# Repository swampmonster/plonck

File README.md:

# plonck

An attempt at making a planck-compatible pcb with bluetooth  

## Current status:
### Rev A0 (NOT RECOMMENDED FOR PRODUCTION, READ STATUS)
I've received and built this version and it works fine but i made the mistake of wiring up the GND and VBUS pins on the ESD chip incorrectly.  
Thankfully those are the middle pins and simply desoldering and turning the chip around solves the problem.  
Update: Finally had time to test the load sharing circuitry and i had the pinout of the mosfet setup incorrectly which requires bodge wires to fix.  
If you are looking to get boards made from this revision you need to be aware of this but my recommendation would be to wait for the next one.

## Rev B0
This should address all the issues in A0 while also adding some features that were not previously present such as:  
- Leds for charge and bootloader status.
- Voltage divider for charge monitoring.
- SMD USB port so it can be mounted by JLC.

Boards have been ordered but not yet received so production is still not recommended.

## License
The project is licensed under [CERN-OHL-S](LICENSE) (see [LICENSE](LICENSE) file) with the exceptions of:
- The [MX_Alps_Hybrid](MX_Alps_Hybrid) directory which is licensed under the [MIT License](https://opensource.org/licenses/MIT) and is made by [ai03](https://github.com/ai03-2725/MX_Alps_Hybrid).
- The [USB4085-GF-A_REVA](USB4085-GF-A_REVA) directory which is licensed under the [Creative Commons Attribution-ShareAlike 4.0 International License](https://creativecommons.org/licenses/by-sa/4.0/) and comes from [SnapEDA](https://www.snapeda.com/parts/USB4085-GF-A/Global%20Connector%20Technology/view-part/?ref=global%20connector%20technology_in&t=usb4085).
- The [PTS525SM15SMTR2LFS](PTS525SM15SMTR2LFS) directory which is licensed under the [Creative Commons Attribution-ShareAlike 4.0 International License](https://creativecommons.org/licenses/by-sa/4.0/) and comes from [SnapEDA](https://www.snapeda.com/parts/PTS525SM15SMTR2%20LFS/C&K/view-part/?ref=search&t=PTS525).
- The [SM02B-SRSS-TB_LF__SN_](SM02B-SRSS-TB_LF__SN_) directory which is licensed under the [Creative Commons Attribution-ShareAlike 4.0 International License](https://creativecommons.org/licenses/by-sa/4.0/) and comes from [SnapEDA](https://www.snapeda.com/parts/SM02B-SRSS-TB%28LF%29%28SN%29/JST%20Sales/view-part/447499).
- The [ul_SI2301CDST1GE3](ul_SI2301CDST1GE3) directory which is licensed under the terms provided in the Terms and Conditions on [Ultra Librarian](https://www.ultralibrarian.com/)

## Thanks
Huge shoutout to [4pplet](https://github.com/4pplet) for tons of advice and help.

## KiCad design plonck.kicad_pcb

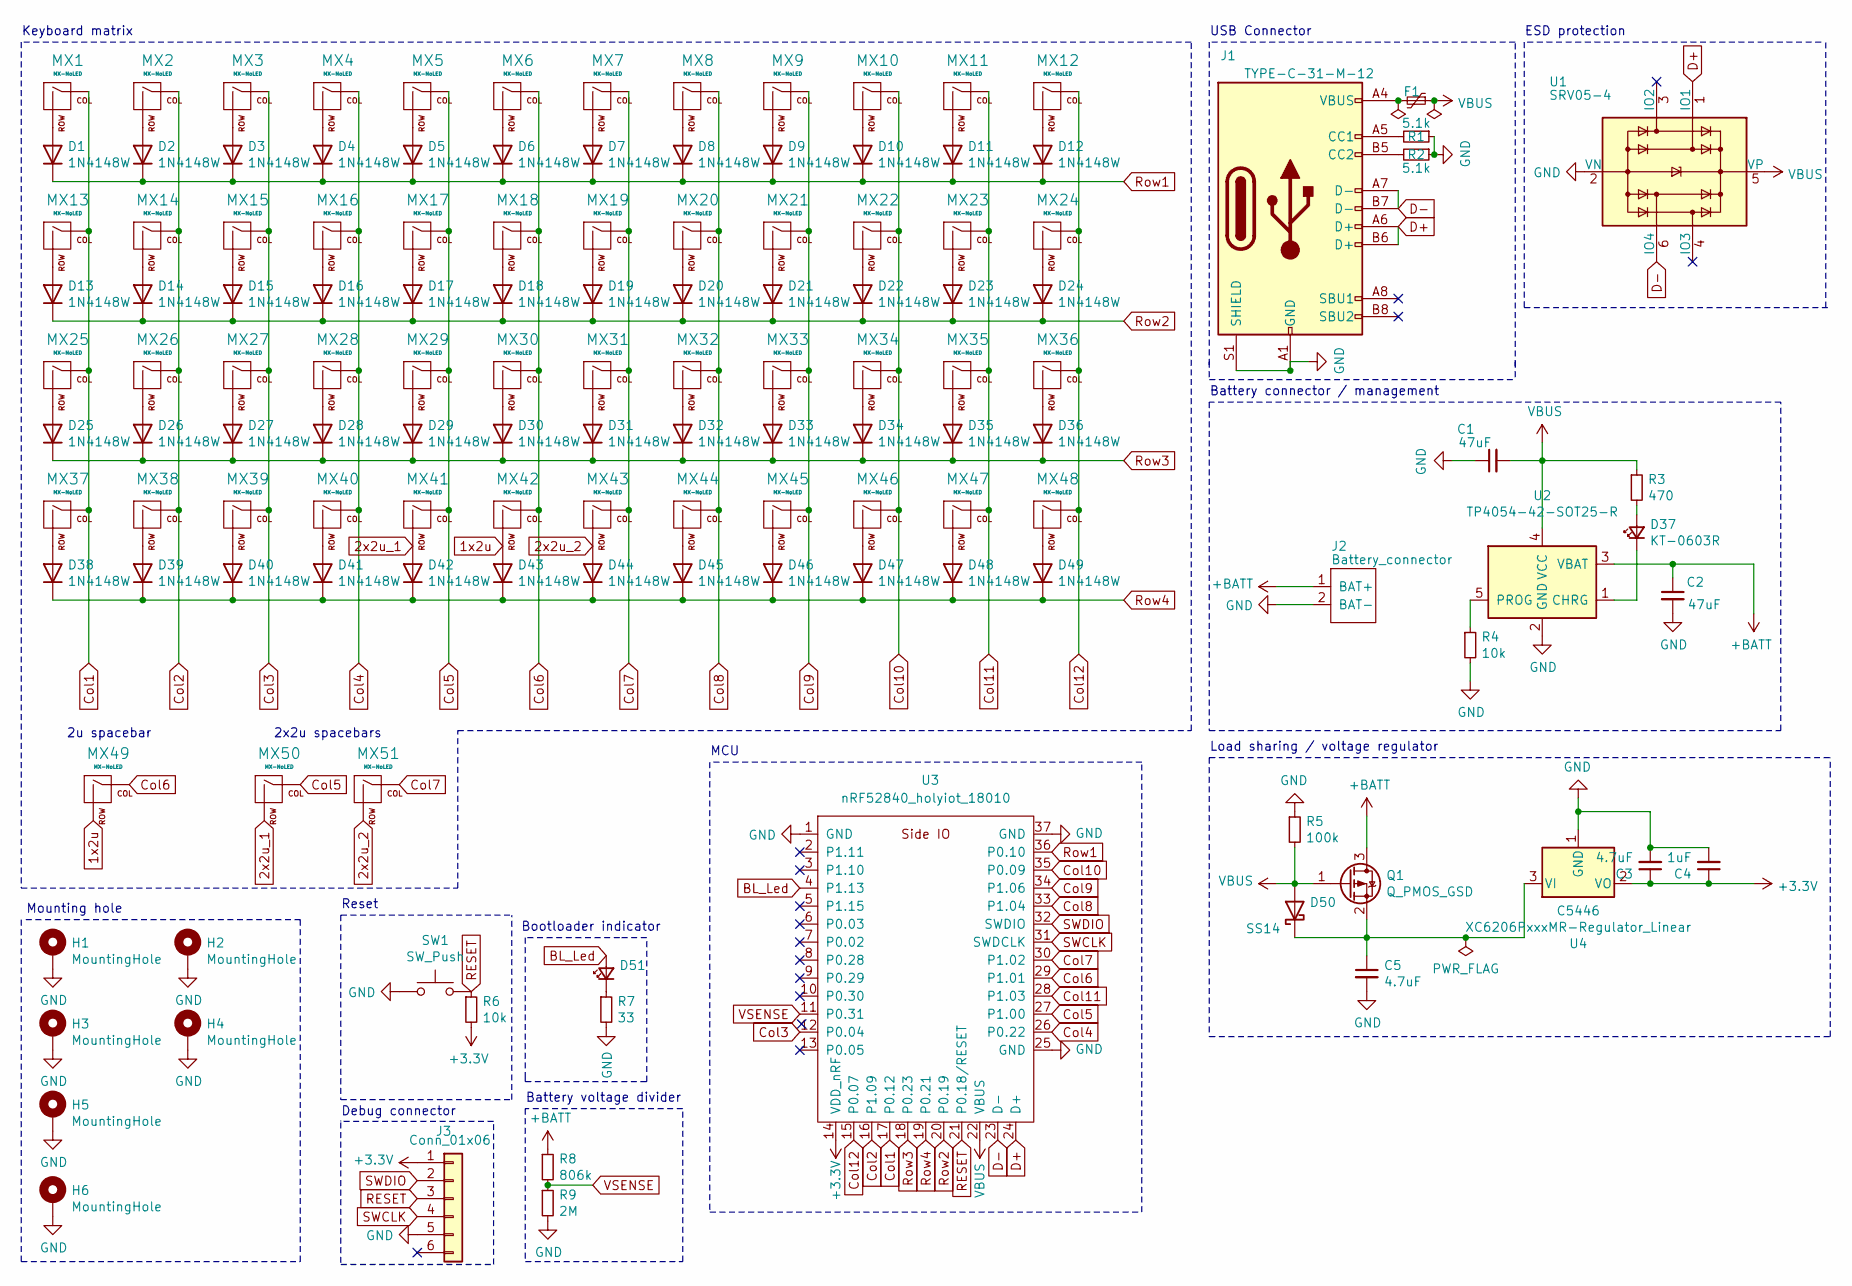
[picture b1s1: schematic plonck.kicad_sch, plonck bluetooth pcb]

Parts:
C1, C2: 47uF; C_1206_3216Metric; LCSC C96123
C3, C5: 4.7uF; C_0603_1608Metric; LCSC C19666
C4: 1uF; C_0603_1608Metric; LCSC C15849
D1, D2, D3, D4, D5, D6, D7, D8, D9, D10, D11, D12, D13, D14, D15, D16, D17, D18, D19, D20, D21, D22, D23, D24, D25, D26, D27, D28, D29, D30, D31, D32, D33, D34, D35, D36, D38, D39, D40, D41, D42, D43, D44, D45, D46, D47, D48, D49: 1N4148W; D_SOD-123; LCSC C402213
D37: KT-0603R; LED_0603_1608Metric; LCSC C2286
D50: SS14; D_SMA; LCSC C2480
D51: 19-217/BHC-ZL1M2RY/3T; LED_0603_1608Metric; LCSC C72041
F1: SMD Fuse Fast Blow 500mA; Fuse_1206_3216Metric; LCSC C182974
H1, H2, H3, H4, H5, H6: MountingHole; MountingHole_2.7mm_M2.5_Pad_TopBottom
J1: TYPE-C-31-M-12; USB_C_Receptacle_HRO_TYPE-C-31-M-12; LCSC C165948
J2: Battery_connector; SM02B-SRSS-TB(LF)(SN)
J3: Conn_01x06; Tag-Connect_TC2030-IDC-NL_2x03_P1.27mm_Vertical
MX1, MX2, MX3, MX4, MX5, MX6, MX7, MX8, MX9, MX10, MX11, MX12, MX13, MX14, MX15, MX16, MX17, MX18, MX19, MX20, MX21, MX22, MX23, MX24, MX25, MX26, MX27, MX28, MX29, MX30, MX31, MX32, MX33, MX34, MX35, MX36, MX37, MX38, MX39, MX40, MX41, MX42, MX43, MX44, MX45, MX46, MX47, MX48: MX-NoLED; MX-1U-NoLED
MX49, MX50, MX51: MX-NoLED; MX-2U-ReversedStabilizers-NoLED
Q1: Q_PMOS_GSD; SI2301CDS-T1-GE3; LCSC C10487
R1, R2: 5.1k; R_0603_1608Metric; Digikey RMCF0603JT5K10TR-ND
R3: 470; R_0603_1608Metric; Digikey RMCF0603JT470RTR-ND
R4, R6: 10k; R_0603_1608Metric; LCSC C25804
R5: 100k; R_0603_1608Metric; Digikey RMCF0603JG100KTR-ND
R7: 33; R_0603_1608Metric; LCSC C23140
R8: 806k; R_0603_1608Metric; LCSC C23250
R9: 2M; R_0603_1608Metric; LCSC C22976
SW1: SW_Push; SW_Push_SPST_NO_Alps_SKRK; LCSC C115357
U1: SRV05-4; SOT-23-6; LCSC C782797
U2: TP4054-42-SOT25-R; TSOT-23-5; LCSC C32574
U3: nRF52840_holyiot_18010; nRF52840_holyiot_18010_HS_simple
U4: XC6206PxxxMR-Regulator_Linear; SOT-23; LCSC C5446

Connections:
1x2u: D43.2 (A), MX42.2 (ROW), MX49.2 (ROW)
2x2u_1: D42.2 (A), MX41.2 (ROW), MX50.2 (ROW)
2x2u_2: D44.2 (A), MX43.2 (ROW), MX51.2 (ROW)
+3V3: C3.1, C4.1, J3.1, R6.2, U3.14 (VDD_nRF), U4.2 (VO)
+BATT: C2.1, J2.1 (BAT+), Q1.3 (D), R8.1, U2.3 (VBAT)
BL_Led: D51.2 (A), U3.4 (P1.13)
Col1: MX1.1 (COL), MX13.1 (COL), MX25.1 (COL), MX37.1 (COL), U3.17 (P0.12)
Col2: MX2.1 (COL), MX14.1 (COL), MX26.1 (COL), MX38.1 (COL), U3.16 (P1.09)
Col3: MX3.1 (COL), MX15.1 (COL), MX27.1 (COL), MX39.1 (COL), U3.12 (P0.04)
Col4: MX4.1 (COL), MX16.1 (COL), MX28.1 (COL), MX40.1 (COL), U3.26 (P0.22)
Col5: MX5.1 (COL), MX17.1 (COL), MX29.1 (COL), MX41.1 (COL), MX50.1 (COL), U3.27 (P1.00)
Col6: MX6.1 (COL), MX18.1 (COL), MX30.1 (COL), MX42.1 (COL), MX49.1 (COL), U3.29 (P1.01)
Col7: MX7.1 (COL), MX19.1 (COL), MX31.1 (COL), MX43.1 (COL), MX51.1 (COL), U3.30 (P1.02)
Col8: MX8.1 (COL), MX20.1 (COL), MX32.1 (COL), MX44.1 (COL), U3.33 (P1.04)
Col9: MX9.1 (COL), MX21.1 (COL), MX33.1 (COL), MX45.1 (COL), U3.34 (P1.06)
Col10: MX10.1 (COL), MX22.1 (COL), MX34.1 (COL), MX46.1 (COL), U3.35 (P0.09)
Col11: MX11.1 (COL), MX23.1 (COL), MX35.1 (COL), MX47.1 (COL), U3.28 (P1.03)
Col12: MX12.1 (COL), MX24.1 (COL), MX36.1 (COL), MX48.1 (COL), U3.15 (P0.07)
D+: J1.A6 (D+), J1.B6 (D+), U1.1 (IO1), U3.24 (D+)
D-: J1.A7 (D-), J1.B7 (D-), U1.6 (IO4), U3.23 (D-)
GND: C1.1, C2.2, C3.2, C4.2, C5.2, H1.1, H2.1, H3.1, H4.1, H5.1, H6.1, J1.A1 (GND), J1.A12 (GND), J1.B1 (GND), J1.B12 (GND), J1.S1 (SHIELD), J2.2 (BAT-), J2.3, J2.4, J3.5, R1.1, R2.1, R4.2, R5.1, R7.2, R9.2, SW1.1, U1.2 (VN), U2.2 (GND), U3.1 (GND), U3.25 (GND), U3.37 (GND), U4.1 (GND)
unnamed: C5.1, D50.1, Q1.2 (S), U4.3 (VI)
unnamed: D1.2 (A), MX1.2 (ROW)
unnamed: D2.2 (A), MX2.2 (ROW)
unnamed: D3.2 (A), MX3.2 (ROW)
unnamed: D4.2 (A), MX4.2 (ROW)
unnamed: D5.2 (A), MX5.2 (ROW)
unnamed: D6.2 (A), MX6.2 (ROW)
unnamed: D7.2 (A), MX7.2 (ROW)
unnamed: D8.2 (A), MX8.2 (ROW)
unnamed: D9.2 (A), MX9.2 (ROW)
unnamed: D10.2 (A), MX10.2 (ROW)
unnamed: D11.2 (A), MX11.2 (ROW)
unnamed: D12.2 (A), MX12.2 (ROW)
unnamed: D13.2 (A), MX13.2 (ROW)
unnamed: D14.2 (A), MX14.2 (ROW)
unnamed: D15.2 (A), MX15.2 (ROW)
unnamed: D16.2 (A), MX16.2 (ROW)
unnamed: D17.2 (A), MX17.2 (ROW)
unnamed: D18.2 (A), MX18.2 (ROW)
unnamed: D19.2 (A), MX19.2 (ROW)
unnamed: D20.2 (A), MX20.2 (ROW)
unnamed: D21.2 (A), MX21.2 (ROW)
unnamed: D22.2 (A), MX22.2 (ROW)
unnamed: D23.2 (A), MX23.2 (ROW)
unnamed: D24.2 (A), MX24.2 (ROW)
unnamed: D25.2 (A), MX25.2 (ROW)
unnamed: D26.2 (A), MX26.2 (ROW)
unnamed: D27.2 (A), MX27.2 (ROW)
unnamed: D28.2 (A), MX28.2 (ROW)
unnamed: D29.2 (A), MX29.2 (ROW)
unnamed: D30.2 (A), MX30.2 (ROW)
unnamed: D31.2 (A), MX31.2 (ROW)
unnamed: D32.2 (A), MX32.2 (ROW)
unnamed: D33.2 (A), MX33.2 (ROW)
unnamed: D34.2 (A), MX34.2 (ROW)
unnamed: D35.2 (A), MX35.2 (ROW)
unnamed: D36.2 (A), MX36.2 (ROW)
unnamed: D37.1 (K), U2.1 (CHRG)
unnamed: D37.2 (A), R3.2
unnamed: D38.2 (A), MX37.2 (ROW)
unnamed: D39.2 (A), MX38.2 (ROW)
unnamed: D40.2 (A), MX39.2 (ROW)
unnamed: D41.2 (A), MX40.2 (ROW)
unnamed: D45.2 (A), MX44.2 (ROW)
unnamed: D46.2 (A), MX45.2 (ROW)
unnamed: D47.2 (A), MX46.2 (ROW)
unnamed: D48.2 (A), MX47.2 (ROW)
unnamed: D49.2 (A), MX48.2 (ROW)
unnamed: D51.1 (K), R7.1
unnamed: F1.2, J1.A4 (VBUS), J1.A9 (VBUS), J1.B4 (VBUS), J1.B9 (VBUS)
unnamed: J1.A5 (CC1), R1.2
unnamed: J1.B5 (CC2), R2.2
unnamed: R4.1, U2.5 (PROG)
RESET: J3.3, R6.1, SW1.2, U3.21 (P0.18/RESET)
Row1: D1.1 (K), D2.1 (K), D3.1 (K), D4.1 (K), D5.1 (K), D6.1 (K), D7.1 (K), D8.1 (K), D9.1 (K), D10.1 (K), D11.1 (K), D12.1 (K), U3.36 (P0.10)
Row2: D13.1 (K), D14.1 (K), D15.1 (K), D16.1 (K), D17.1 (K), D18.1 (K), D19.1 (K), D20.1 (K), D21.1 (K), D22.1 (K), D23.1 (K), D24.1 (K), U3.20 (P0.19)
Row3: D25.1 (K), D26.1 (K), D27.1 (K), D28.1 (K), D29.1 (K), D30.1 (K), D31.1 (K), D32.1 (K), D33.1 (K), D34.1 (K), D35.1 (K), D36.1 (K), U3.18 (P0.23)
Row4: D38.1 (K), D39.1 (K), D40.1 (K), D41.1 (K), D42.1 (K), D43.1 (K), D44.1 (K), D45.1 (K), D46.1 (K), D47.1 (K), D48.1 (K), D49.1 (K), U3.19 (P0.21)
SWCLK: J3.4, U3.31 (SWDCLK)
SWDIO: J3.2, U3.32 (SWDIO)
VBUS: C1.2, D50.2, F1.1, Q1.1 (G), R3.1, R5.2, U1.5 (VP), U2.4 (VCC), U3.22 (VBUS)
VSENSE: R8.2, R9.1, U3.11 (P0.31)

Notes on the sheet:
Keyboard matrix
Mounting hole
2u spacebar
2x2u spacebars
Reset
Debug connector
Bootloader indicator
Battery voltage divider
MCU
USB Connector
Battery connector / management
Load sharing / voltage regulator
ESD protection

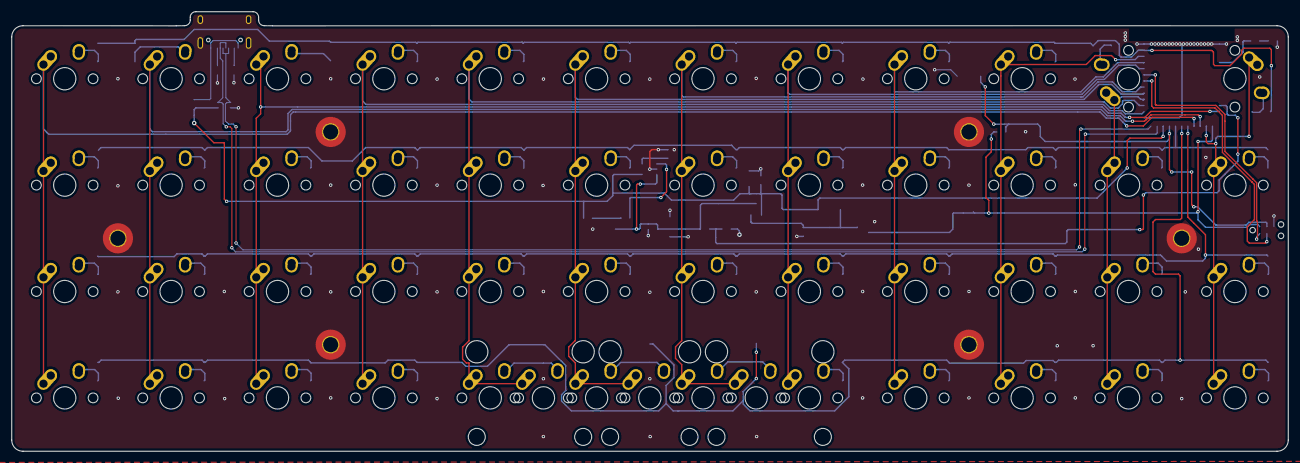
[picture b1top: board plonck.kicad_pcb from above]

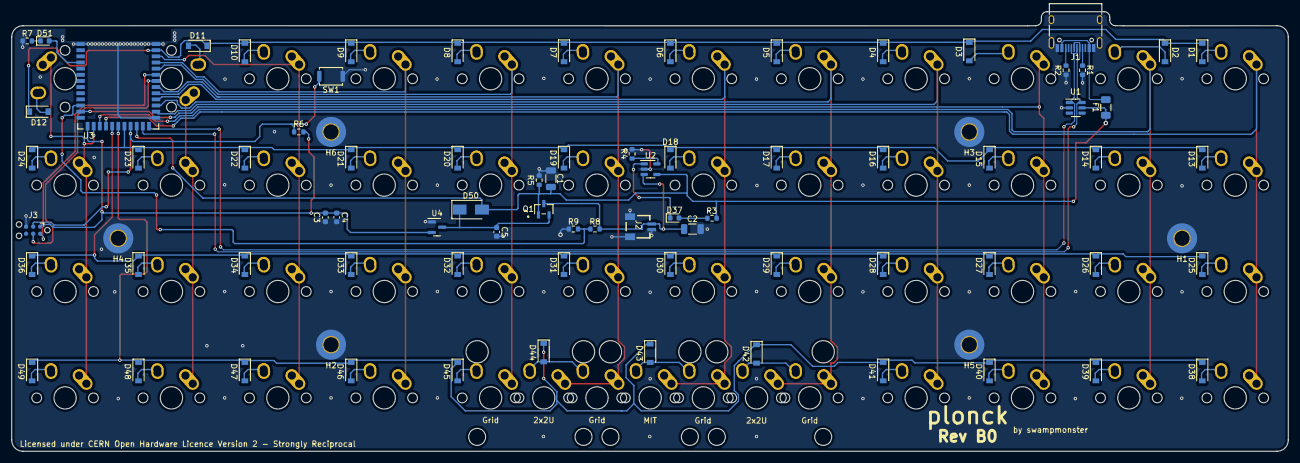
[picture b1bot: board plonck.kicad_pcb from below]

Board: 2 copper layers, 228.6 x 78.7 mm, 132 parts (81 on the bottom side), 83 nets.

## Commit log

2021-04-19 updated some fooprints and added lcsc part numbers
2021-04-20 added ground fill on top layer
2021-04-20 updated parts and fixed ground fill
2021-04-22 fixing up via sizes and ground planes
2021-04-22 added missing lcsc part number
2021-04-24 bunch of fixes and changes to use only basic parts from lcsc
2021-04-26 updated board render
2021-05-14 rescue stuff
2021-05-23 various fixes and additions
    changed switch footprints to be alps compatible
    added descriptive text to bottom row
    fixed mounting holes not being connected to ground
    fixed incorrectly wired esd chip
    added reset switch in default planck position
    changed mx3 to normal rotation
2021-06-01 fixed incorrect schematic symbol for mosfet
2021-06-01 added charge status led
2021-06-01 added vsense circuitry
2021-06-02 updated resistor values in battery voltage divider
2021-06-03 added bootloader status led
2021-06-07 updated resistor values for vsense
    https://devzone.nordicsemi.com/nordic/nordic-blog/b/blog/posts/measuring-lithium-battery-voltage-with-nrf52
2021-06-08 added symbols for battery connector
2021-06-08 changed battery connector to smaller size
2021-06-20 updating ignores for new version of kicad
2021-06-20 bunch of updates and fixes related to new kicad version
2021-06-20 more fixing
2021-06-20 added holyiot module footprint
2021-06-20 updated board revision
2021-06-20 more more fixing
2021-06-22 various updates
    * switched to smd usb-c port
    * updated various lcsc part numbers
2021-06-23 adding/fixing lcsc part numbers
2021-06-24 housekeeping

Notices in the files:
plonck.kicad_pcb:
Licensed under CERN Open Hardware Licence Version 2 - Strongly Reciprocal
parts and their libraries:
Copyright 2016 Accelerated Designs. All rights reserved.
